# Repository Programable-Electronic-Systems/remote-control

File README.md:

remote-control
==============

Proyecto de ejemplo basado en un mando remoto universal

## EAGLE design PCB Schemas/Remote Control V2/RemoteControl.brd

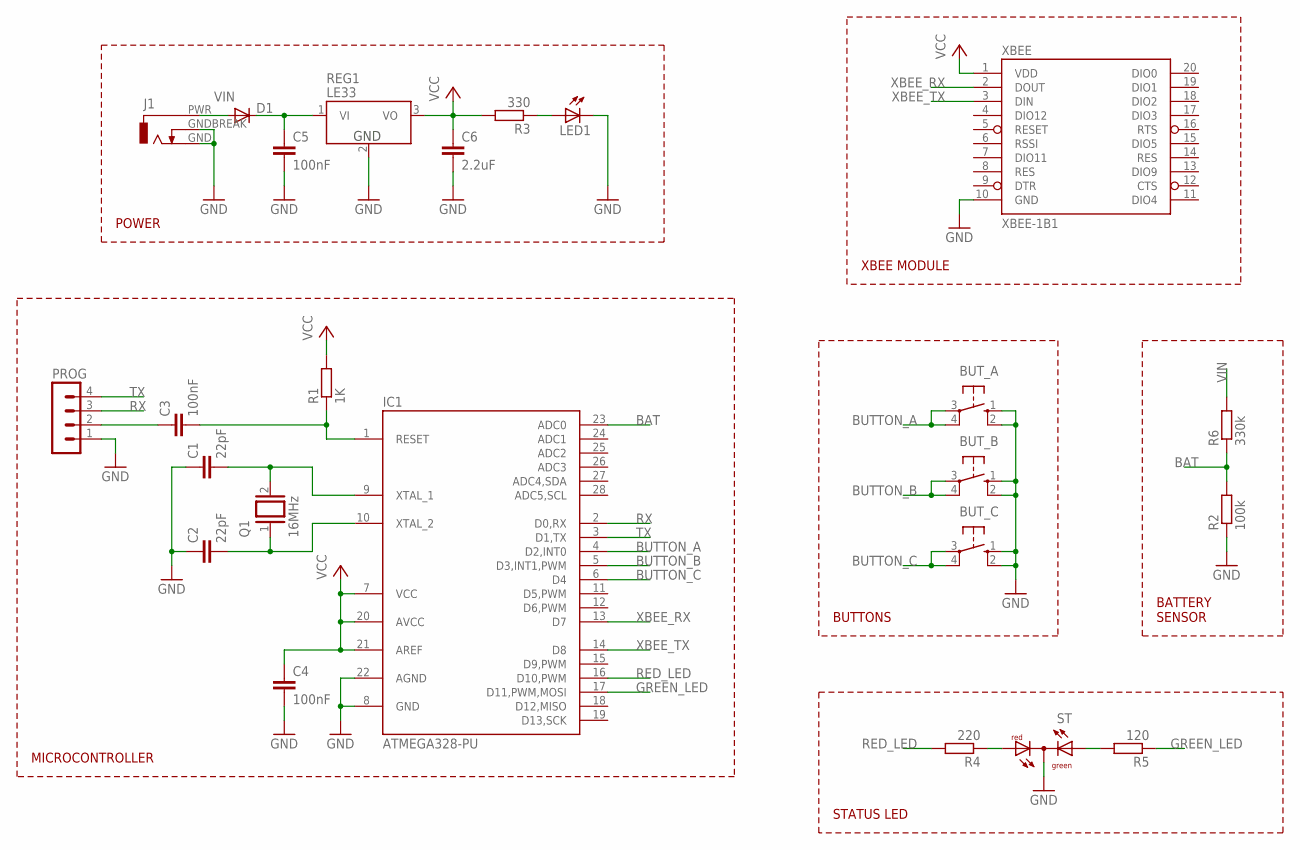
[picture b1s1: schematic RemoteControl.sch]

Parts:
BUT_A: 40-XX; B3F-40XX
BUT_B: 40-XX; B3F-40XX
BUT_C: 40-XX; B3F-40XX
C1, C2: 22pF; C050-024X044
C3, C4, C5: 100nF; C050-025X075
C6: 2.2uF; C050-035X075
D1: 1N4148DO35-7; DO35-7
IC1: ATMEGA328-PU; DIL28-3
J1: DC_JACKPTH; POWER_JACK_PTH
LED1: LED3MM
PROG: MA04-1
Q1: 16MHz; QS
R1: 1K; 0207/7
R2: 100k; 0207/7
R3: 330; 0207/7
R4: 220; 0207/7
R5: 120; 0207/7
R6: 330k; 0207/7
REG1: LE33; TO-92
ST: DUOLED-RG-C; DUOLED-C-5MM
XBEE: XBEE-1B1; XBEE-1

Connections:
BAT: IC1.23 (ADC0), R2.2, R6.1
BUTTON_A: BUT_A.3, BUT_A.4 (P1), IC1.4 (D2,INT0)
BUTTON_B: BUT_B.3, BUT_B.4 (P1), IC1.5 (D3,INT1,PWM)
BUTTON_C: BUT_C.3, BUT_C.4 (P1), IC1.6 (D4)
GND: BUT_A.1 (S), BUT_A.2 (S1), BUT_B.1 (S), BUT_B.2 (S1), BUT_C.1 (S), BUT_C.2 (S1), C1.1, C2.1, C4.2, C5.2, C6.2, IC1.8 (GND), IC1.22 (AGND), J1.GND (3), J1.GNDBREAK (2), LED1.K (C), PROG.1, R2.1, REG1.2 (GND), ST.C, XBEE.10 (GND)
GREEN_LED: IC1.17 (D11,PWM,MOSI), R5.1
unnamed: C1.2, IC1.9 (XTAL_1), Q1.2
unnamed: C2.2, IC1.10 (XTAL_2), Q1.1
unnamed: C5.1, D1.C, REG1.1 (VI)
unnamed: C3.2, IC1.1 (RESET), R1.1
unnamed: C3.1, PROG.2
unnamed: LED1.A, R3.1
unnamed: R4.1, ST.AR
unnamed: R5.2, ST.AX (AG)
RED_LED: IC1.16 (D10,PWM), R4.2
RX: IC1.2 (D0,RX), PROG.3
TX: IC1.3 (D1,TX), PROG.4
VCC: C4.1, C6.1, IC1.7 (VCC), IC1.20 (AVCC), IC1.21 (AREF), R1.2, R3.2, REG1.3 (VO), XBEE.1 (VDD)
VIN: D1.A, J1.PWR (1), R6.2
XBEE_RX: IC1.13 (D7), XBEE.2 (DOUT)
XBEE_TX: IC1.14 (D8), XBEE.3 (DIN)

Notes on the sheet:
POWER
BUTTONS
BATTERY SENSOR
XBEE MODULE
STATUS LED
MICROCONTROLLER

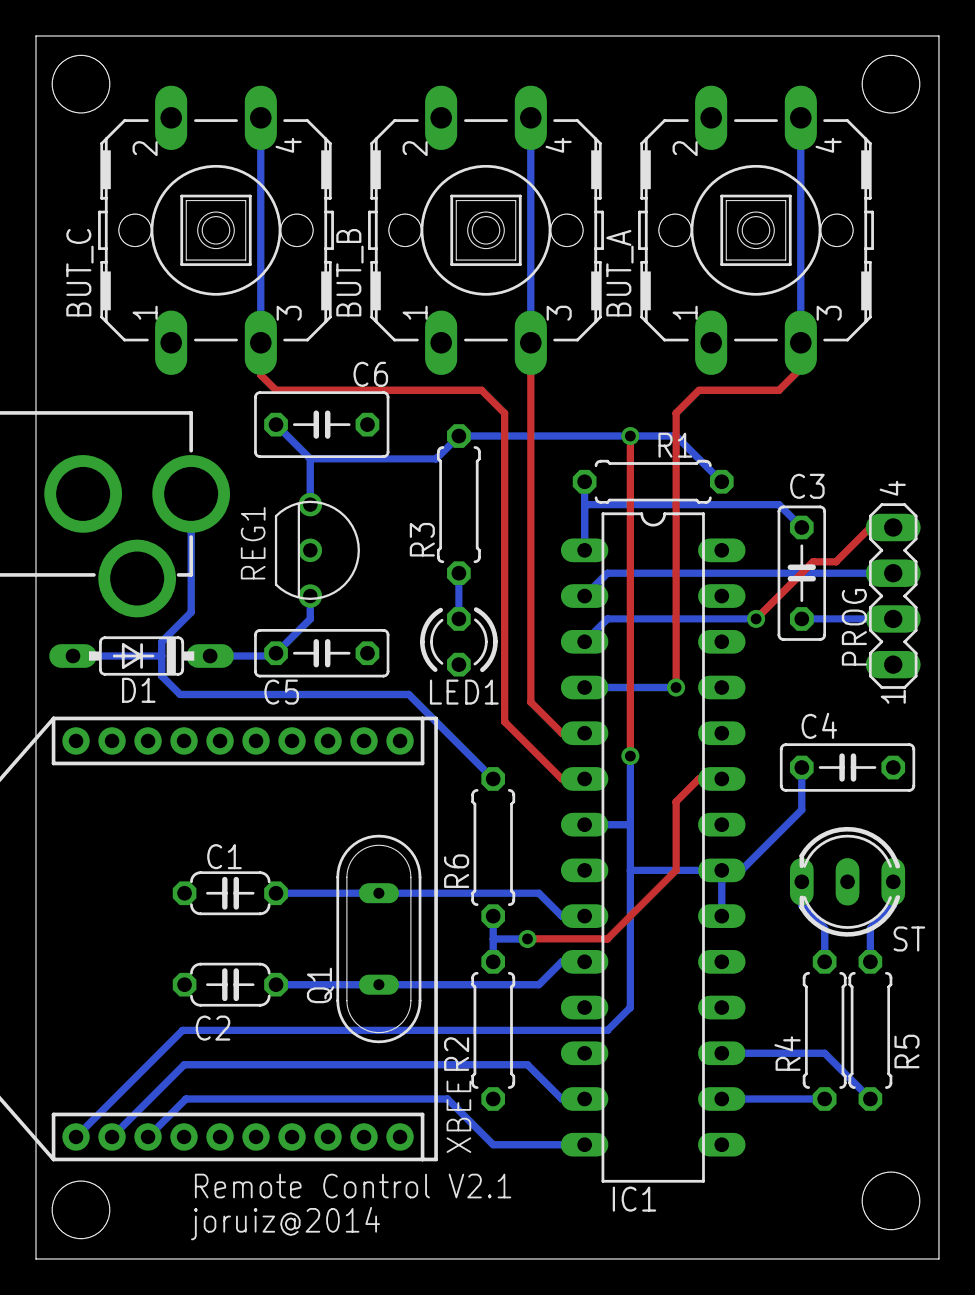
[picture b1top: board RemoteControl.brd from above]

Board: 2 copper layers, 50.2 x 67.9 mm, 24 parts (0 on the bottom side), 21 nets.

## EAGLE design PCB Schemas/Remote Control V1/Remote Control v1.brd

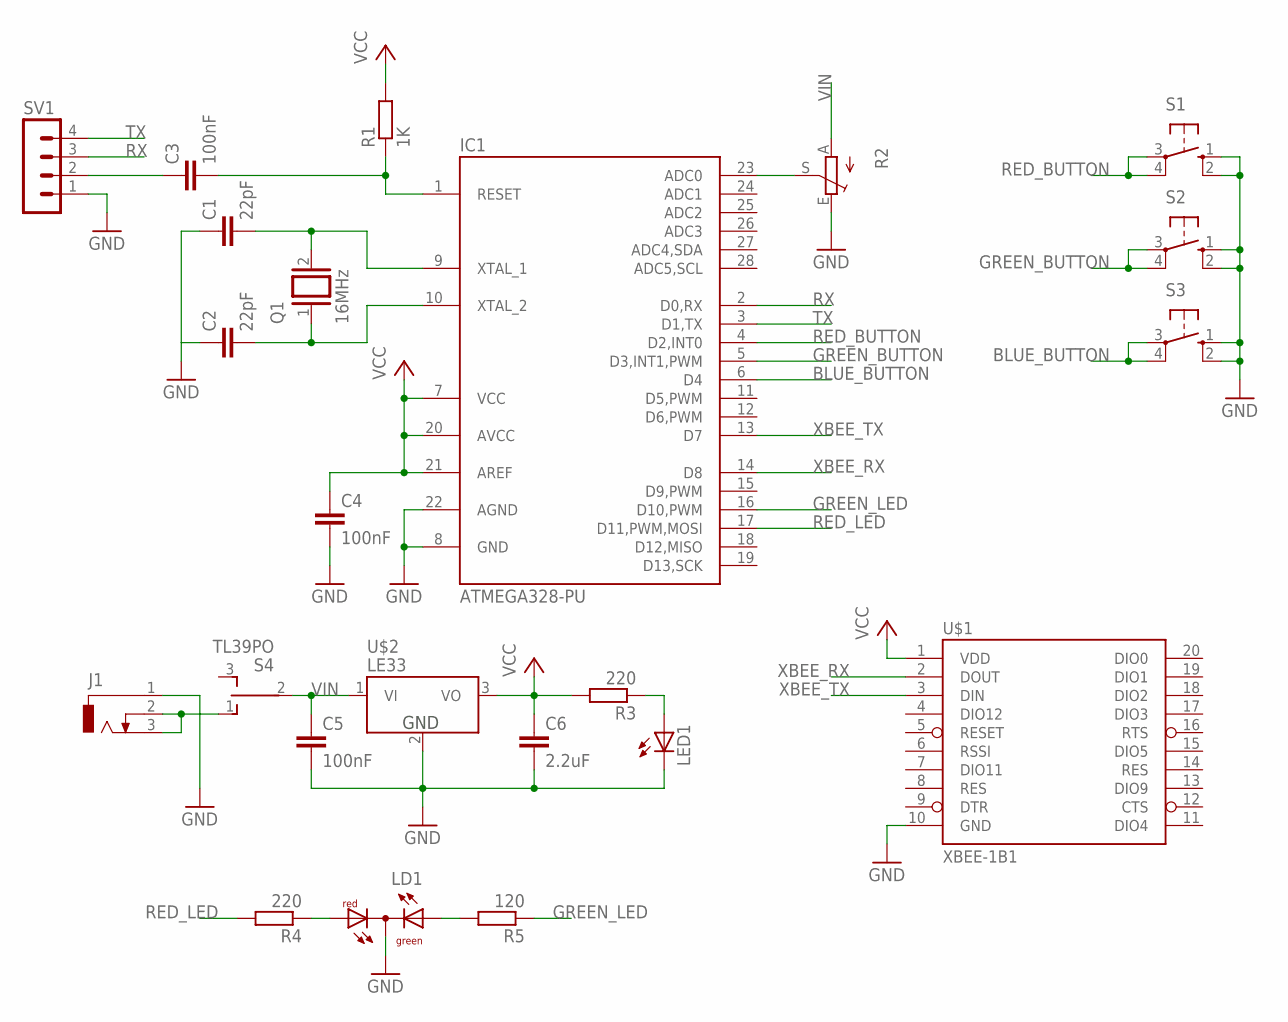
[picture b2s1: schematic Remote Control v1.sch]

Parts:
C1, C2: 22pF; C050-024X044
C3, C4, C5: 100nF; C050-025X075
C6: 2.2uF; C050-035X075
IC1: ATMEGA328-PU; DIL28-3
J1: DCJ0303
LD1: DUOLED-RG-C; DUOLED-C-5MM
LED1: LED3MM
Q1: 16MHz; QS
R1: 1K; 0207/7
R2: TRIM_EU-CA9V; CA9V
R3, R4: 220; 0207/7
R5: 120; 0207/7
S1, S2, S3: 40-XX; B3F-40XX
S4: TL39PO; TL3XPO
SV1: MA04-1
U$1: XBEE-1B1; XBEE-1
U$2: LE33; TO-92

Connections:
BLUE_BUTTON: IC1.6 (D4), S3.3, S3.4 (P1)
GND: C1.1, C2.1, C4.2, C5.2, C6.2, IC1.8 (GND), IC1.22 (AGND), J1.1, LD1.C, LED1.K (C), R2.E, S1.1 (S), S1.2 (S1), S2.1 (S), S2.2 (S1), S3.1 (S), S3.2 (S1), SV1.1, U$1.10 (GND), U$2.2 (GND)
GREEN_BUTTON: IC1.5 (D3,INT1,PWM), S2.3, S2.4 (P1)
GREEN_LED: IC1.16 (D10,PWM), R5.1
unnamed: C1.2, IC1.9 (XTAL_1), Q1.2
unnamed: C2.2, IC1.10 (XTAL_2), Q1.1
unnamed: J1.2, J1.3, S4.1 (O)
unnamed: C3.2, IC1.1 (RESET), R1.1
unnamed: C3.1, SV1.2
unnamed: IC1.23 (ADC0), R2.S
unnamed: LED1.A, R3.1
unnamed: LD1.AR, R4.1
unnamed: LD1.AX (AG), R5.2
RED_BUTTON: IC1.4 (D2,INT0), S1.3, S1.4 (P1)
RED_LED: IC1.17 (D11,PWM,MOSI), R4.2
RX: IC1.2 (D0,RX), SV1.3
TX: IC1.3 (D1,TX), SV1.4
VCC: C4.1, C6.1, IC1.7 (VCC), IC1.20 (AVCC), IC1.21 (AREF), R1.2, R3.2, U$1.1 (VDD), U$2.3 (VO)
VIN: C5.1, R2.A, S4.2, U$2.1 (VI)
XBEE_RX: IC1.14 (D8), U$1.2 (DOUT)
XBEE_TX: IC1.13 (D7), U$1.3 (DIN)

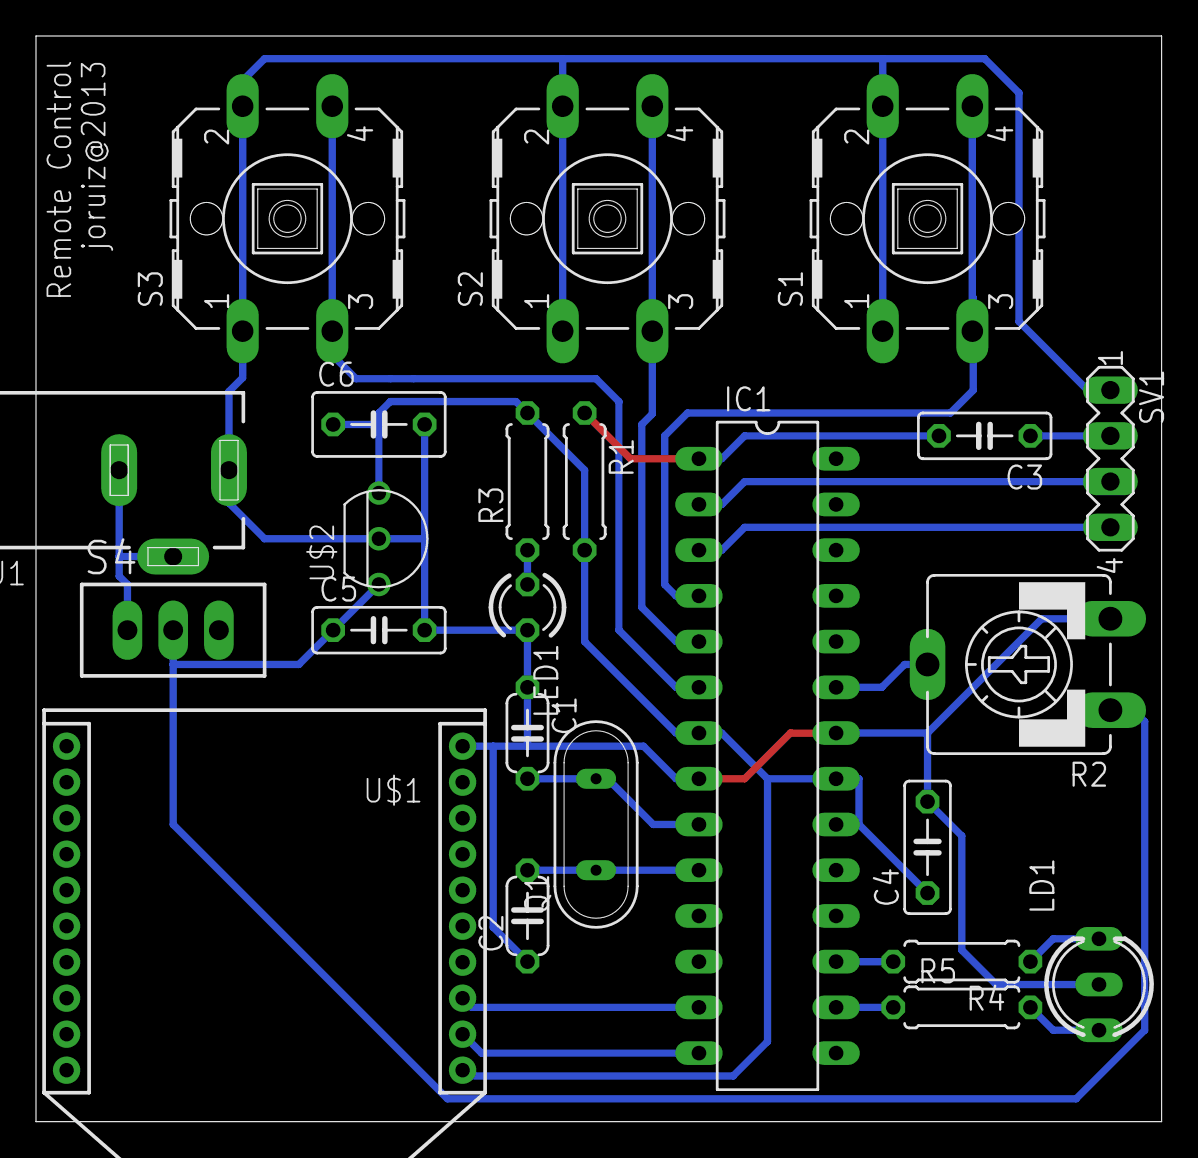
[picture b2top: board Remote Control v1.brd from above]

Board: 2 copper layers, 62.5 x 60.3 mm, 23 parts (0 on the bottom side), 21 nets.

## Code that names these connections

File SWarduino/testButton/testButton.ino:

#define BUTTON_A  2
#define BUTTON_B  3
#define BUTTON_C  4

void setup() {

  Serial.begin(9600);
  pinMode(BUTTON_A, INPUT_PULLUP);
  pinMode(BUTTON_B, INPUT_PULLUP);
  pinMode(BUTTON_C, INPUT_PULLUP);
  Serial.println("Start Button Test Program");
}

void loop() {

  if (digitalRead(BUTTON_A) ==  LOW)
      Serial.println("Button A activated.");
  if (digitalRead(BUTTON_B) ==  LOW)
      Serial.println("Button B activated.");
  if (digitalRead(BUTTON_C) ==  LOW)
      Serial.println("Button C activated.");
  delay(100);
}

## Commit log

2013-10-30 Cargado el proyecto completo del mando remoto universal
2013-11-13 Updated license file
2014-11-13 Finalized V1 and V2 of remote control
2014-12-21 Revised PCB schemas for V1 and V2
